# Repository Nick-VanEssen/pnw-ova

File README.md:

# Purdue-Northwest-Vibration-Analysis
Vibration Analysis senior design project for Purdue Northwest.

# Background
Household appliances breaking down is a costly issue for everyday consumers. 
There are typically two options when an appliance breaks down: reactive maintenance or buying a replacement, both of which are extremely costly. Proactive maintenance, as opposed to reactive maintenance, is identifying and fixing the issue before it results in a breakdown. Industries, such as the steel industry for example, have been investing in monitoring equipment on their machinery to identify and fix issues before they cause a total breakdown. Individual consumers do not yet have this luxury, so oftentimes their appliances completely break before they are aware of an issue.

# Objective
The open vibration analysis project seeks to prevent reactive maintenance of consumer appliances and instead allow the owners to perform proactive maintenance. Reactive maintenance, which is fixing the problem after it breaks down, is almost always more costly and time consuming than proactive maintenance, which is fixing a problem before it results in a complete breakdown. The objective of this project is to build a device that would be able to identify the problem before it results in a breakdown and alert the consumer to fix it. This would save the consumer money and reduce downtime. 

# Approach
The vibration analysis device would work by being attached to the consumer appliance.  It would use a combination of an accelerometer, to measure vibration, and a contact microphone, to measure sound. These measurements would be analyzed in a custom software that will be able to recognize any abnormalities in vibration or sound. That way, if the appliance begins to show signs of an imminent breakdown, the device will alert the user.

# Outcome
The anticipated outcome is a relatively small device, around 5”x5”, that can easily be attached to a consumer appliance, connected to a power supply, and easily configured with a user-friendly software. This software could connect to a phone and send notification alerts when the device senses abnormalities in the appliance. The device would ideally serve a wide range of consumers and work with most home appliances, such as washing/drying machines, refrigerators, AC units, and more.

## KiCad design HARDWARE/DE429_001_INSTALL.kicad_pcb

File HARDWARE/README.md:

# HARDWARE 
Sensors:

Accelerometer: ADXL345    
    
Microphone: SPH0645

Microprocessor/Bluetooth and WiFi Module:  ESP32-WROOM-32D

USB Bridge controller: CP2102 USB to UART

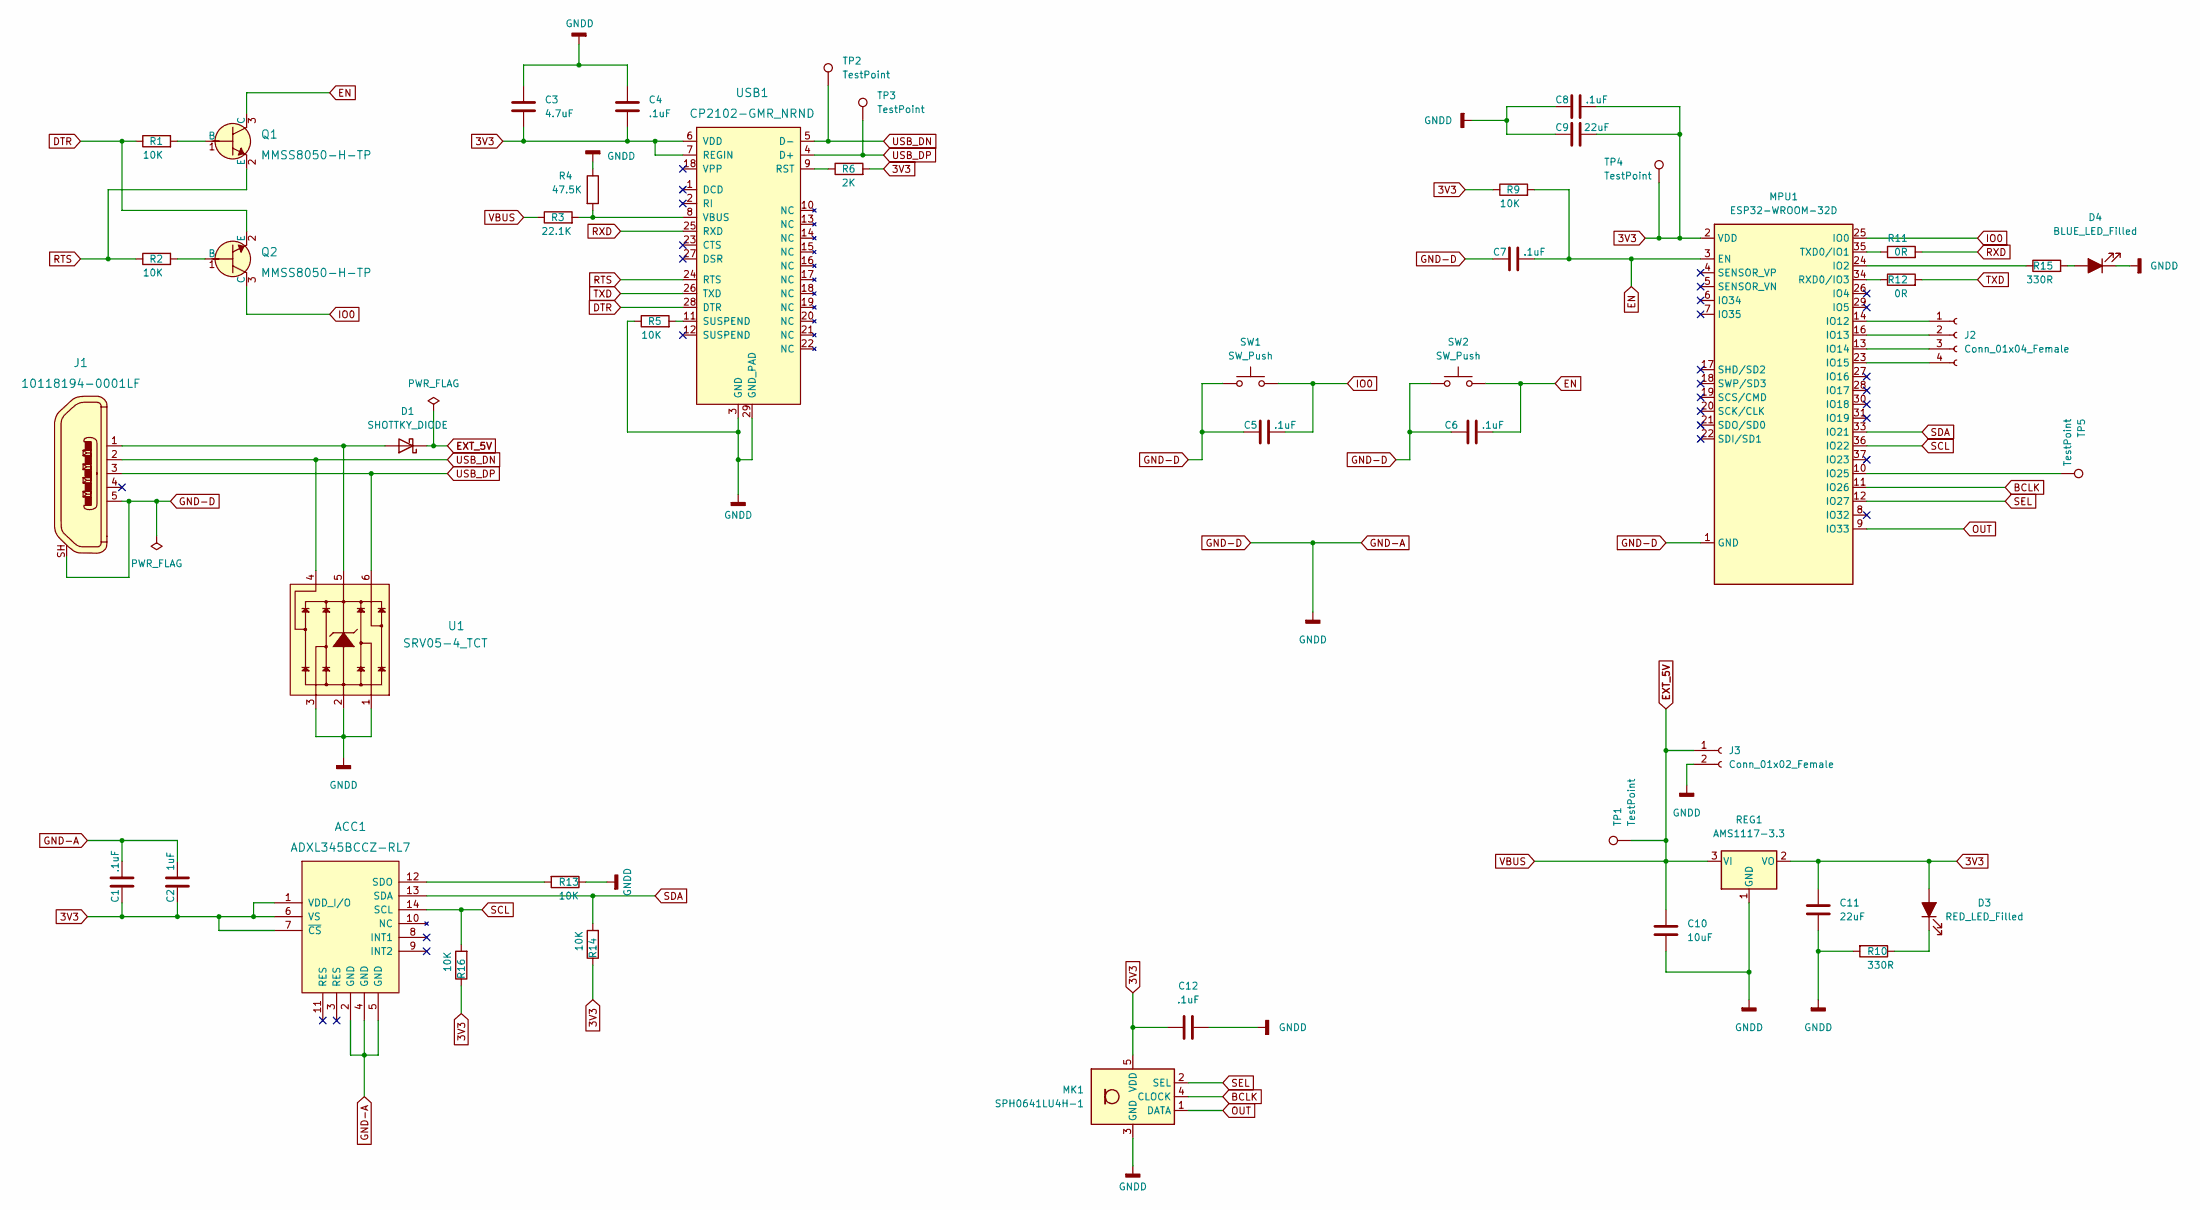
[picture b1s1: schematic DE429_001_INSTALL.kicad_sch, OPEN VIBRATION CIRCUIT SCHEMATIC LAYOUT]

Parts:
ACC1: ADXL345BCCZ-RL7; LGA-14_3x5mm_RevA; MPN ADXL345BCCZ-RL7; Digi-Key_PN ADXL345BCCZ-RL7CT-ND
C1, C4, C5, C6, C7, C8, C12: .1uF; C_0603_1608Metric
C2: 1uF; C_0603_1608Metric
C3: 4.7uF; C_0603_1608Metric
C9, C11: 22uF; C_0603_1608Metric
C10: 10uF; C_0603_1608Metric
D1: SHOTTKY_DIODE; D_SMA
D3: RED_LED_Filled; LED_0603_1608Metric
D4: BLUE_LED_Filled; LED_0603_1608Metric
J1: 10118194-0001LF; USB_Micro_B_Female_10118194-0001LF; MPN 10118194-0001LF; Digi-Key_PN 609-4618-1-ND
J2: Conn_01x04_Female; JST_XH_B4B-XH-AM_1x04_P2.50mm_Vertical
J3: Conn_01x02_Female; JST_XH_B2B-XH-AM_1x02_P2.50mm_Vertical
MK1: SPH0641LU4H-1; Knowles_LGA-5_3.5x2.65mm
MPU1: ESP32-WROOM-32D; ESP32-WROOM-32
Q1, Q2: MMSS8050-H-TP; SOT-23-3; MPN MMSS8050-H-TP; Digi-Key_PN MMSS8050-H-TPMSCT-ND
R1, R2, R5, R9, R13, R14, R16: 10K; R_0603_1608Metric
R3: 22.1K; R_0603_1608Metric
R4: 47.5K; R_0603_1608Metric
R6: 2K; R_0603_1608Metric
R10, R15: 330R; R_0603_1608Metric
R11, R12: 0R; R_0603_1608Metric
REG1: AMS1117-3.3; SOT-223-3_TabPin2
SW1, SW2: SW_Push; SW_SPST_TL3342
TP1, TP2, TP3, TP4, TP5: TestPoint; TestPoint_THTPad_D3.0mm_Drill1.5mm
U1: SRV05-4_TCT; SOT-23-6; MPN SRV05-4.TCT; Digi-Key_PN SRV05-4CT-ND
USB1: CP2102-GMR_NRND; VFQFN-28-1EP_5x5mm; MPN CP2102-GMR; Digi-Key_PN 336-1160-1-ND

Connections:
3V3: ACC1.1 (VDD_I/O), ACC1.6 (VS), ACC1.7 (~CS), C1.1, C2.1, C3.2, C4.2, C8.1, C9.1, C11.1, C12.1, D3.2 (A), MK1.5 (VDD), MPU1.2 (VDD), R6.2, R9.1, R14.1, R16.1, REG1.2 (VO), TP4.1, USB1.6 (VDD), USB1.7 (REGIN)
BCLK: MK1.4 (CLOCK), MPU1.11 (IO26)
DTR: Q2.2 (E), R1.1, USB1.28 (DTR)
EN: C6.2, C7.2, MPU1.3 (EN), Q1.3 (C), R9.2, SW2.2
EXT_5V: C10.1, D1.1 (K), J3.1, R3.1, REG1.3 (VI), TP1.1; also elsewhere on the board
GND-A: ACC1.2 (GND), ACC1.4 (GND), ACC1.5 (GND), C1.2, C2.2, C3.1, C4.1, C5.1, C6.1, C7.1, C8.2, C9.2, C10.2, C11.2, C12.2, D4.1 (K), J1.5, J1.SH, J3.2, MK1.3 (GND), MPU1.1 (GND), MPU1.15 (GND), MPU1.38 (GND), MPU1.39 (GND), R4.1, R5.1, R10.2, R13.1, REG1.1 (GND), SW1.1, SW2.1, U1.1, U1.2, U1.3, USB1.3 (GND), USB1.29 (GND_PAD)
IO0: C5.2, MPU1.25 (IO0), Q2.3 (C), SW1.2
unnamed: ACC1.12 (SDO), R13.2
unnamed 8: D1.2 (A), J1.1, U1.5; also elsewhere on the board
unnamed: D3.1 (K), R10.1
unnamed: D4.2 (A), R15.2
unnamed: J2.1, MPU1.14 (IO12)
unnamed: J2.2, MPU1.16 (IO13)
unnamed: J2.3, MPU1.13 (IO14)
unnamed: J2.4, MPU1.23 (IO15)
unnamed: MPU1.10 (IO25), TP5.1
unnamed: MPU1.24 (IO2), R15.1
unnamed: MPU1.34 (RXD0/IO3), R12.1
unnamed: MPU1.35 (TXD0/IO1), R11.1
unnamed: Q1.1 (B), R1.2
unnamed: Q2.1 (B), R2.2
unnamed: R3.2, R4.2, USB1.8 (VBUS)
unnamed: R5.2, USB1.11 (SUSPEND)
unnamed: R6.1, USB1.9 (RST)
OUT: MK1.1 (DATA), MPU1.9 (IO33)
RTS: Q1.2 (E), R2.1, USB1.24 (RTS)
RXD: R11.2, USB1.25 (RXD)
SCL: ACC1.14 (SCL), MPU1.36 (IO22), R16.2
SDA: ACC1.13 (SDA), MPU1.33 (IO21), R14.2
SEL: MK1.2 (SEL), MPU1.12 (IO27)
TXD: R12.2, USB1.26 (TXD)
USB_DN: J1.2, TP2.1, U1.4, USB1.5 (D-)
USB_DP: J1.3, TP3.1, U1.6, USB1.4 (D+)

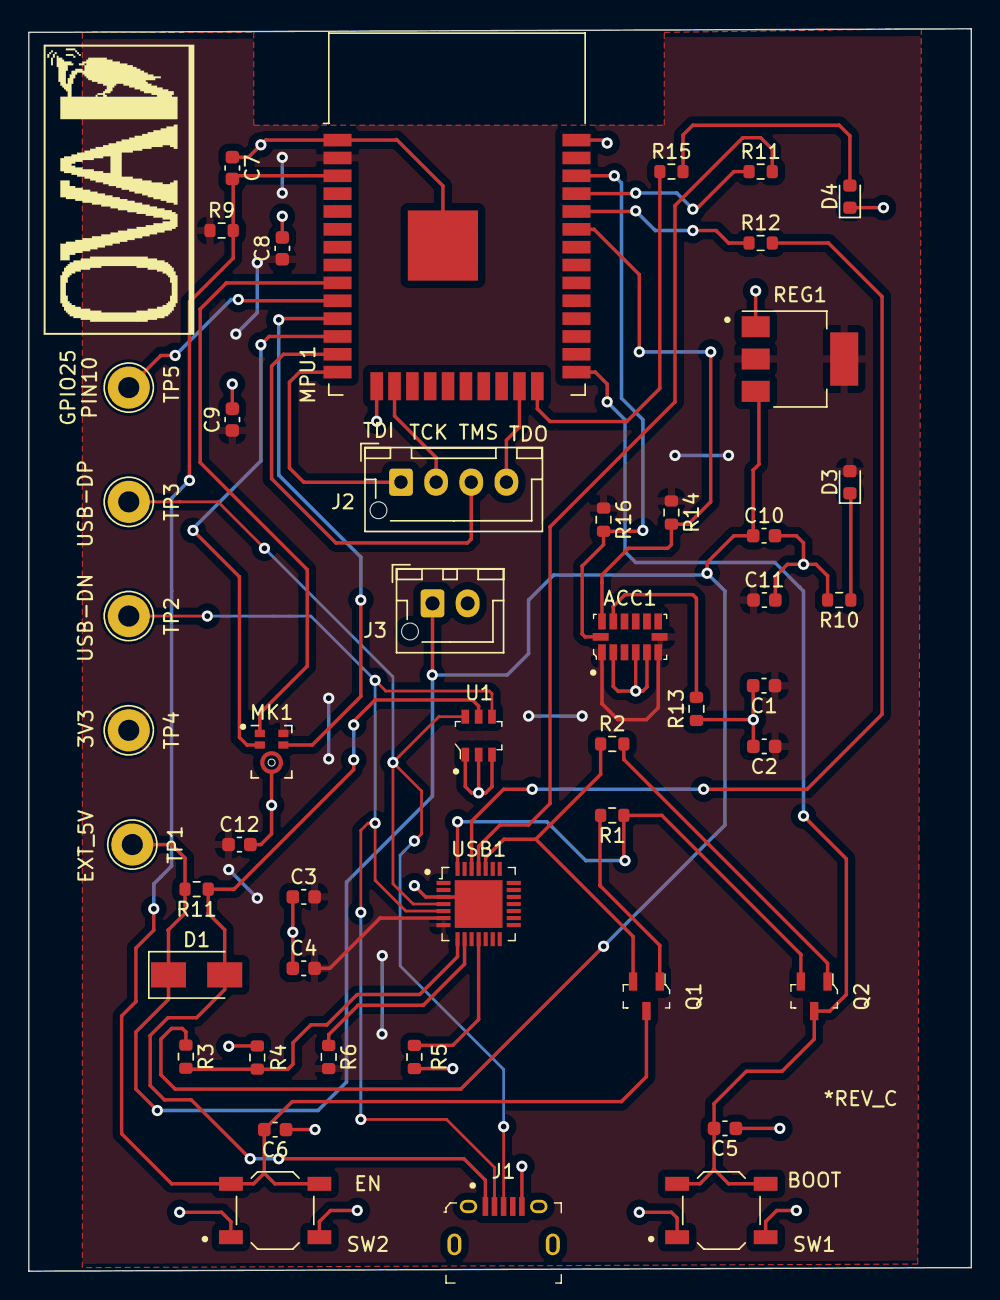
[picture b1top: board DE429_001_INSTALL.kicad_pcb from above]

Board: 2 copper layers, 67.1 x 88.4 mm, 48 parts (0 on the bottom side), 33 nets.

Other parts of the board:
R11#2: 2K; R_0603_1608Metric

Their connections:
EXT_5V: R11#2.2; also elsewhere on the board
unnamed 8: R11#2.1; also elsewhere on the board

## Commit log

2023-10-04 feat: add last years files
    Adds the files from last years repo
2023-10-04 feat: Added ESP32 web server code
2023-10-04 feat: Added websocket
    previously we had async web server, added websocket implementation
2023-10-04 Added header files
    ### Added
    - Added Header Files
    - Added CHANGELOG.md
    - Added gitignore to root of project.
    ### Changed
    - Moved some static assigns to header files.
2023-10-05 feat/ created access point
    Created the access point that we will eventually use to connect the ESP32 to wifi
2023-10-05 test
2023-10-05 junk_Delete_This_Branch
2023-10-05 junk
2023-10-10 Merged Branch "header_file_update" in and worked on wifi setup
    Branch "header_file_update" was merged in, created file wifiSetup.html which will be the file that opens on the access point to connect to wifi.
2023-10-11 Worked on wifi setup access point
2023-10-11 Created Access point and Wifi connection logic
2023-10-18 Moved and cleaned up files, added AXL345 Library
2023-10-18 changed platformio file
2023-10-18 Work on mic code
2023-10-18 feat: new wifi management system
2023-10-19 work on tests
2023-10-19 Folder Maintenance
2023-10-19 fix: esp restart error
2023-10-19 updated gitignore
2023-10-19 added wifi manager to platformio.ini
2023-10-23 Got accelerator data to be passed
2023-10-25 work on reading data off mic
2023-10-26 fork wifimanager branch
2023-10-26 fix: spacing
2023-10-26 fix: more spacing
2023-10-26 feat: new accesspoint name and subheader
2023-10-26 worked on moving acc data along with started fft work
2023-11-02 worked on getting time of system
2023-11-02 creation of time for FFT and added FFTW library
2023-11-04 MEMS PDM Microphone implementation
2023-11-07 attempting to get old board data going
2023-11-07 fixed header issues, working on timing system
2023-11-08 timing worked on
2023-11-08 started with fft
2023-11-09 rough draft email notification code
2023-11-09 Code fix and cleanup
2023-11-09 added FFTW3 library, transferred time to ms, developed ideas to talk about for future
2023-11-09 fix: sender name
2023-11-09 fix: header files and code maintainability
2023-11-10 fix: comment
2023-11-10 restructure a bit and looked at arduinofft library
2023-11-14 fft function: takes in data and does fft (hasnt been tested)
2023-11-16 fix: looping emails
2023-11-16 fft is working
2023-11-16 fixed PR comments
2023-11-16 fft work
2023-11-16 feat: variables setters and getters
2023-11-16 fix: typos
2023-11-26 Added PDM Mic Tasks
    See Changelog.
2023-11-26 Added PDM Stop tasks function.
2023-11-27 fix: email send on every run
2023-11-27 work with arduinoFFT
2023-11-30 work on printing fft
2023-11-30 feat: async web server
2023-11-30 work on output
2023-12-02 acc task work
2023-12-04 feat: web server and graph
2023-12-04 task work
2023-12-04 Tasks created, not complete
2023-12-04 attempting to fix tasks
2023-12-06 changed FFT to not a task and worked on mag problem
2023-12-06 work on data collection and tasks
2023-12-06 Changed variable types
2023-12-06 attempt to fix illegalinstruction error
2023-12-06 Fixed Task issue.
2023-12-06 Changed floats back to double.
2023-12-06 Updated memory usage
2023-12-06 FIXED THE MAGNITUDE GOING TO OVF WOOOOOOOOOOOOOO
2023-12-06 added gravity constant instead of just the number
2023-12-07 feat: half of websocket implementation
2023-12-07 fixed fft errors
2023-12-07 feat: websocket stuff
2023-12-10 feat: half of websocket working
2023-12-10 undo websocket changes and put them on new branch
2023-12-13 Small Fixes?
2024-01-05 called fft function from pdm mic and changed buffer from 200 to 2048
2024-01-18 work on monitor task
2024-01-19 added global arrays and flags
2024-01-22 global variables being updated
2024-01-24 variables stored in micData and accData
2024-01-25 websocket
2024-01-25 websocket stuff. (mag = 0 not finished in main
2024-01-25 mon setup
2024-01-31 classes created, semaphores added and pdm fft data added
2024-02-02 global variables updated correctly
2024-02-07 basline arrays created
2024-02-09 websocket stuff. broken rn
2024-02-10 Fixed immediate crash
2024-02-10 fix memory issues
2024-02-19 fixed output
2024-02-21 working front-end
2024-02-23 Remove Arduino String
2024-02-26 WORKING WEBSOCKET WITH 300 POINTS
2024-03-04 working on saving values to csv
2024-03-06 save to csv method updated
    way to save output is executable > outputfile.txt
2024-03-07 averaged data working
2024-03-08 updated how FFT works
2024-03-14 colors
2024-03-27 testing
2024-03-28 working on ACC timing
2024-03-28 set email input on front end
2024-03-28 Default email to fix crashing if null
2024-03-28 wokr on acc
2024-04-03 setup initial algorithm
2024-04-04 stop start button
2024-04-04 feat: flag for hard coded algo
2024-04-04 quick == fix
2024-04-04 remove heap print
2024-04-05 changed when normalization happened
2024-04-05 feat: hard coded algorithm!
2024-04-05 added email variable and import in fft file
2024-04-05 fixes
2024-04-25 feat: addons
2024-04-25 a few changes
